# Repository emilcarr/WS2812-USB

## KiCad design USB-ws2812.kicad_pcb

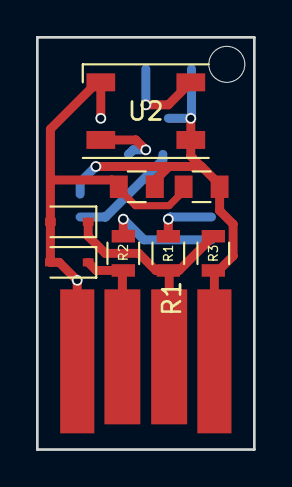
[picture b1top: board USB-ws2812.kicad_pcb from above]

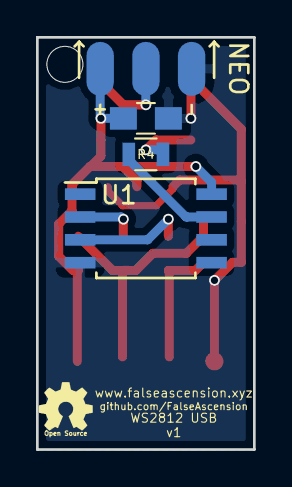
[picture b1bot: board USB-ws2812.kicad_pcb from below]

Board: 2 copper layers, 12.1 x 22.9 mm, 13 parts (4 on the bottom side), 9 nets.

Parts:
C1: 0.1uF; C_0805
C2: 10uF; C_0805
C3: 0.1uF; C_0805_HandSoldering
D1, D2: 3.6V Zener; D_SOD-323
J1: USB; usb-PCB
J2: NEO
R1, R2: 68R; R_0805
R3: 1K5; R_0805
R4: R; R_0805
U1: ATTINY85-20PU; SOIJ-8_5.3x5.3mm_Pitch1.27mm
U2: WS2812B; LED_WS2812B-PLCC4

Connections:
+5V: C1.1, C2.1, C3.2, J1.1, J2.3, R3.1, U1.8, U2.1
/D+: D2.1, J1.3, R2.2
/D-: D1.1, J1.2, R1.2, R3.2
/I_D+: R2.1, U1.3
/I_D-: R1.1, U1.2
/NEO_I: R4.1, U2.4
/NEO_O: J2.2, U2.2
/PB2: R4.2, U1.7
GND: C1.2, C2.2, C3.1, D1.2, D2.2, J1.4, J2.1, U1.4, U2.3

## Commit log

2017-12-29 Initial
2017-12-30 POWER CONNECTOR
2017-12-30 Fix careless mistakes (ZzZZZZzzzzz)
2018-01-21 New, smaller design
